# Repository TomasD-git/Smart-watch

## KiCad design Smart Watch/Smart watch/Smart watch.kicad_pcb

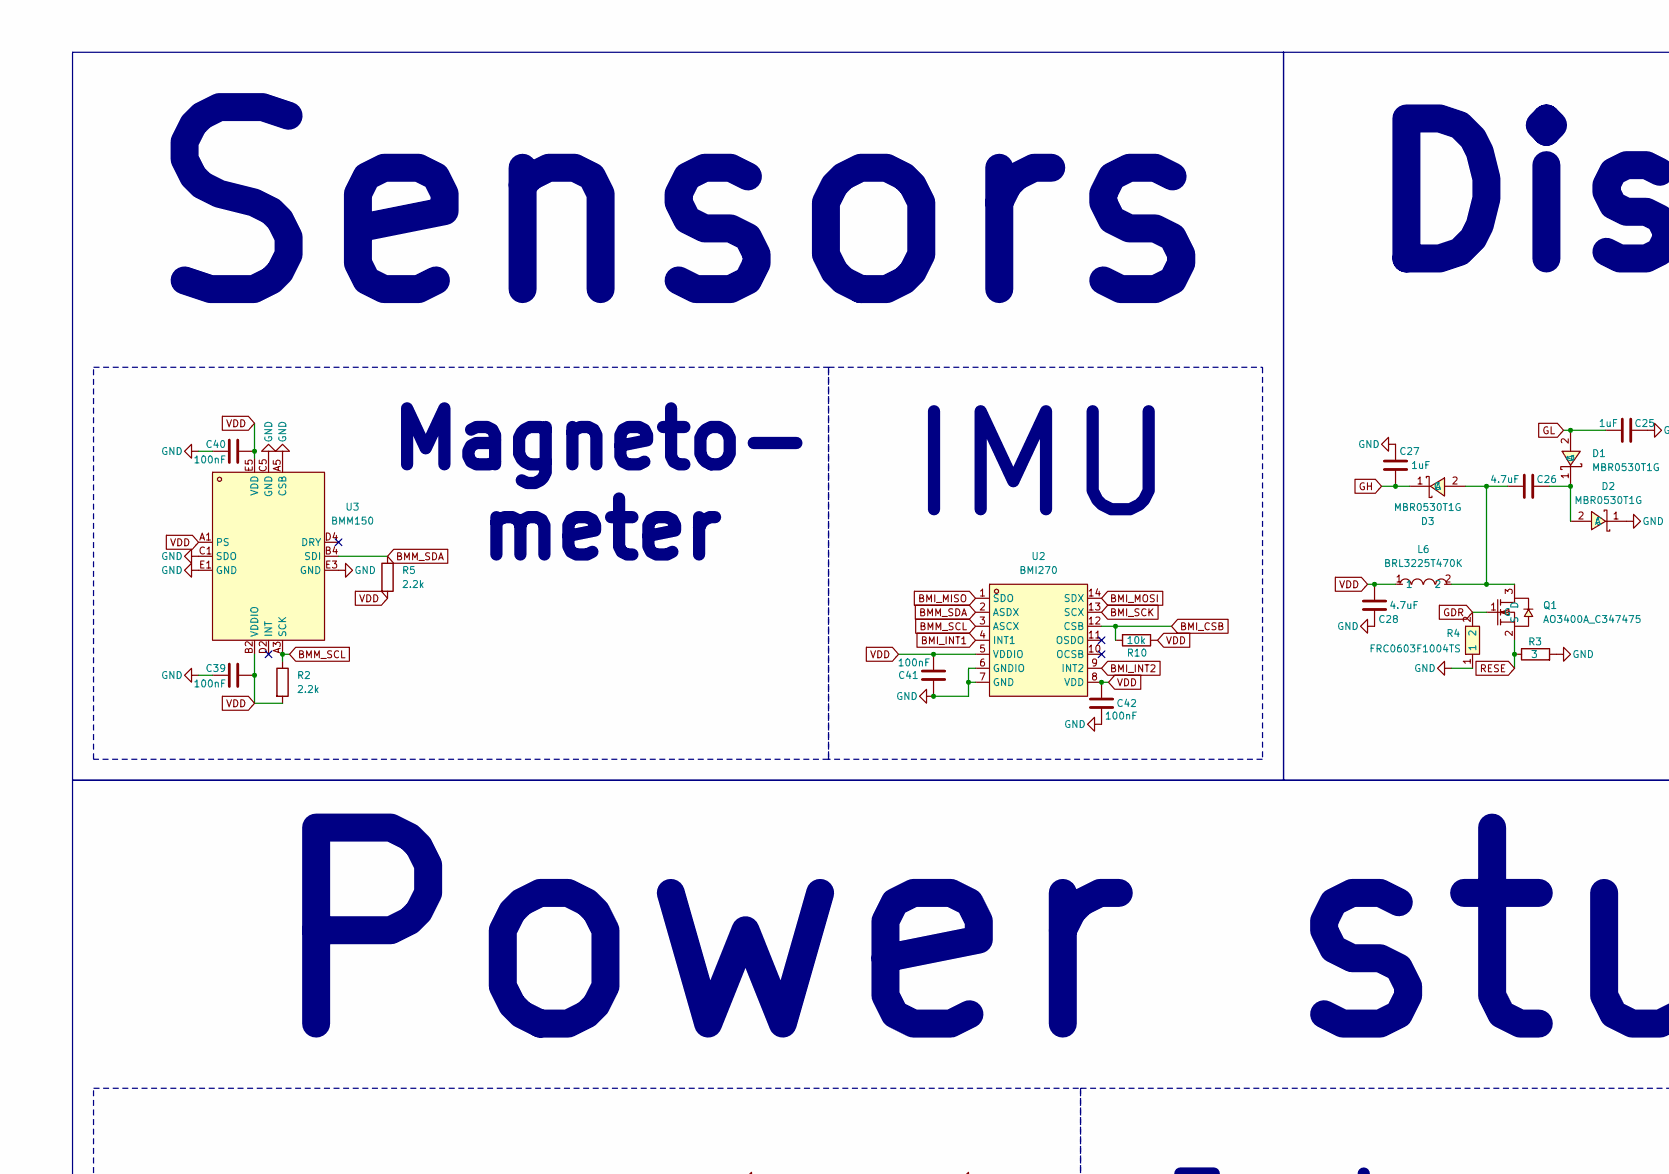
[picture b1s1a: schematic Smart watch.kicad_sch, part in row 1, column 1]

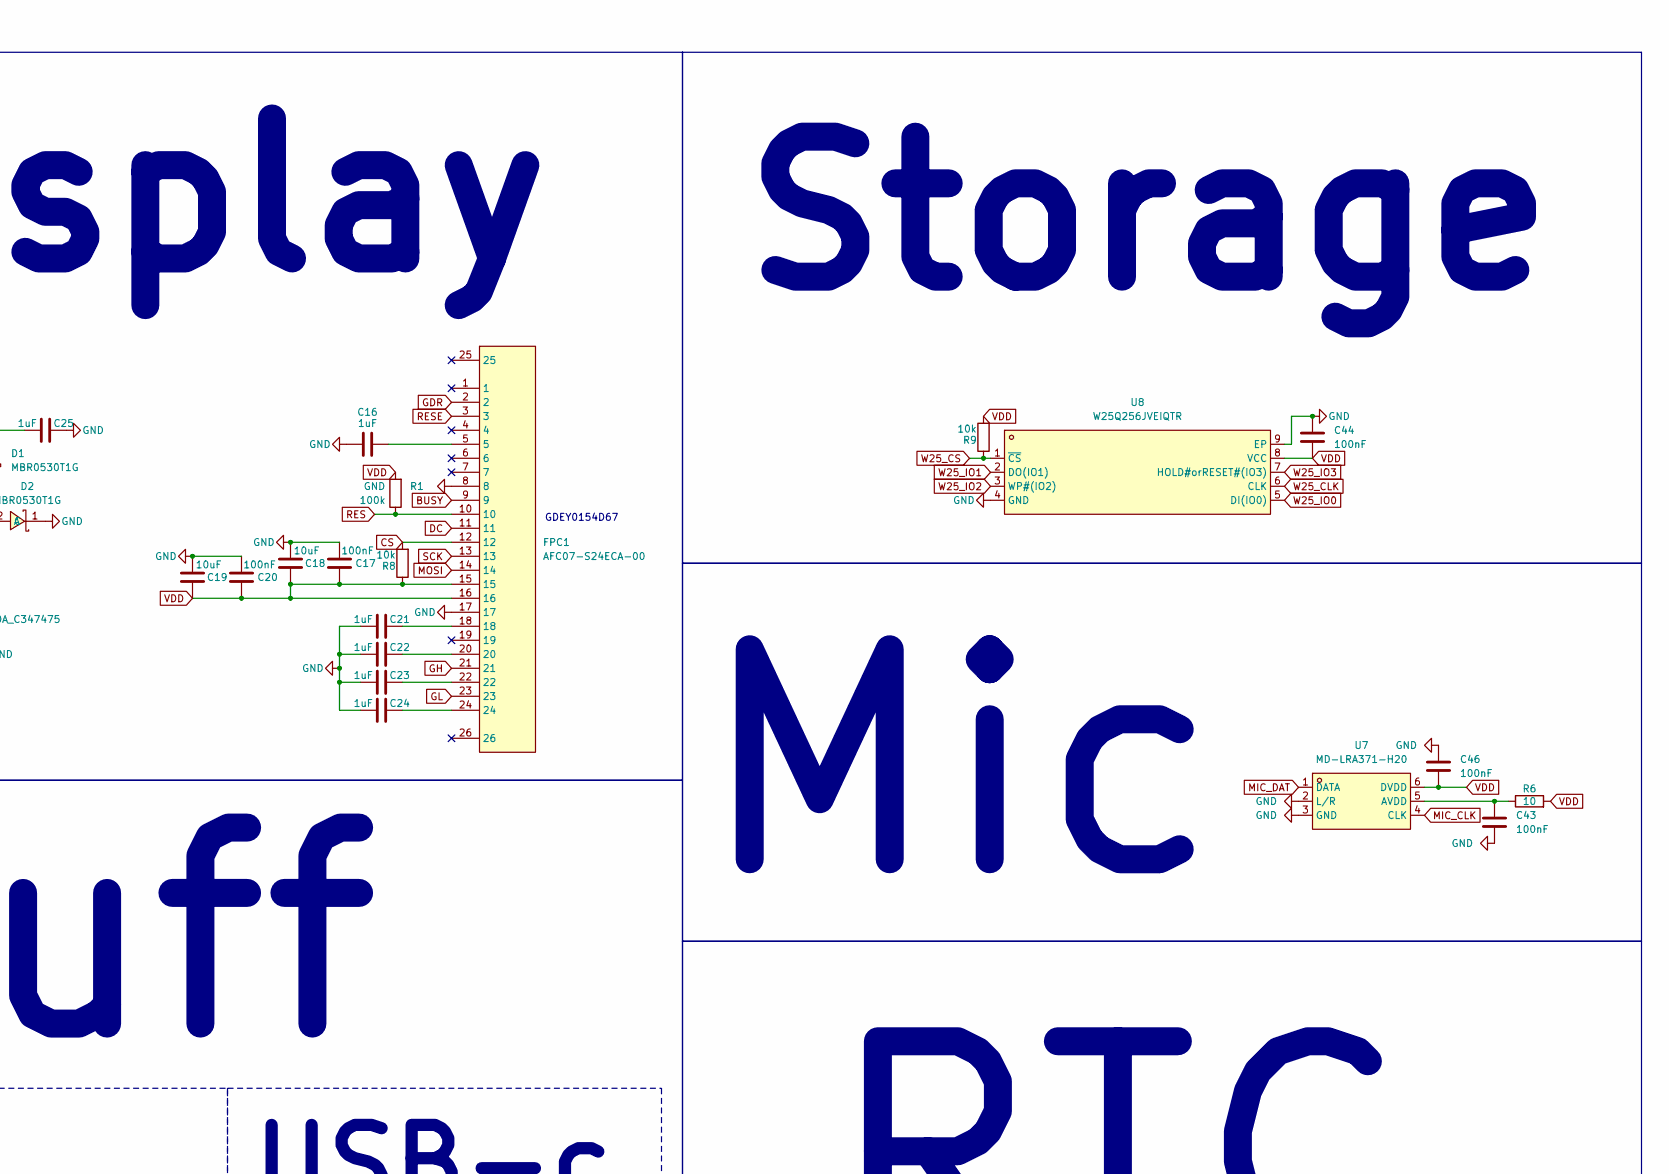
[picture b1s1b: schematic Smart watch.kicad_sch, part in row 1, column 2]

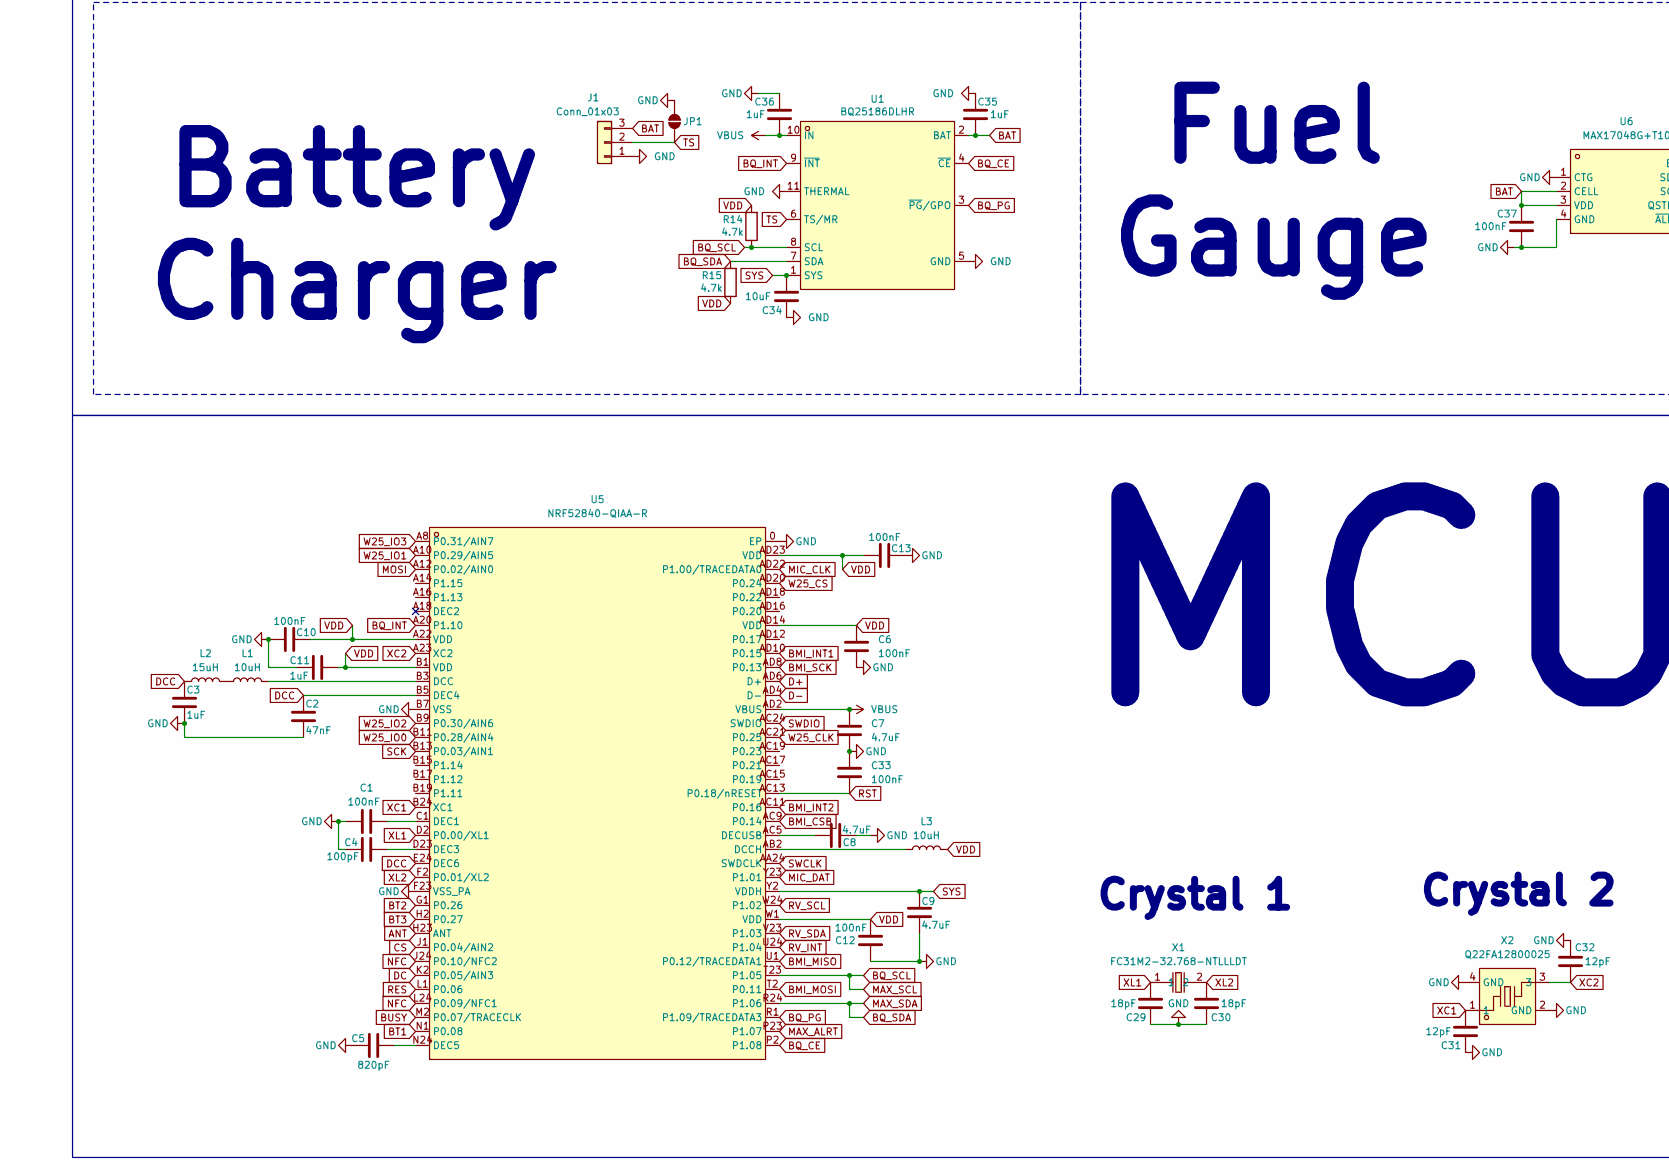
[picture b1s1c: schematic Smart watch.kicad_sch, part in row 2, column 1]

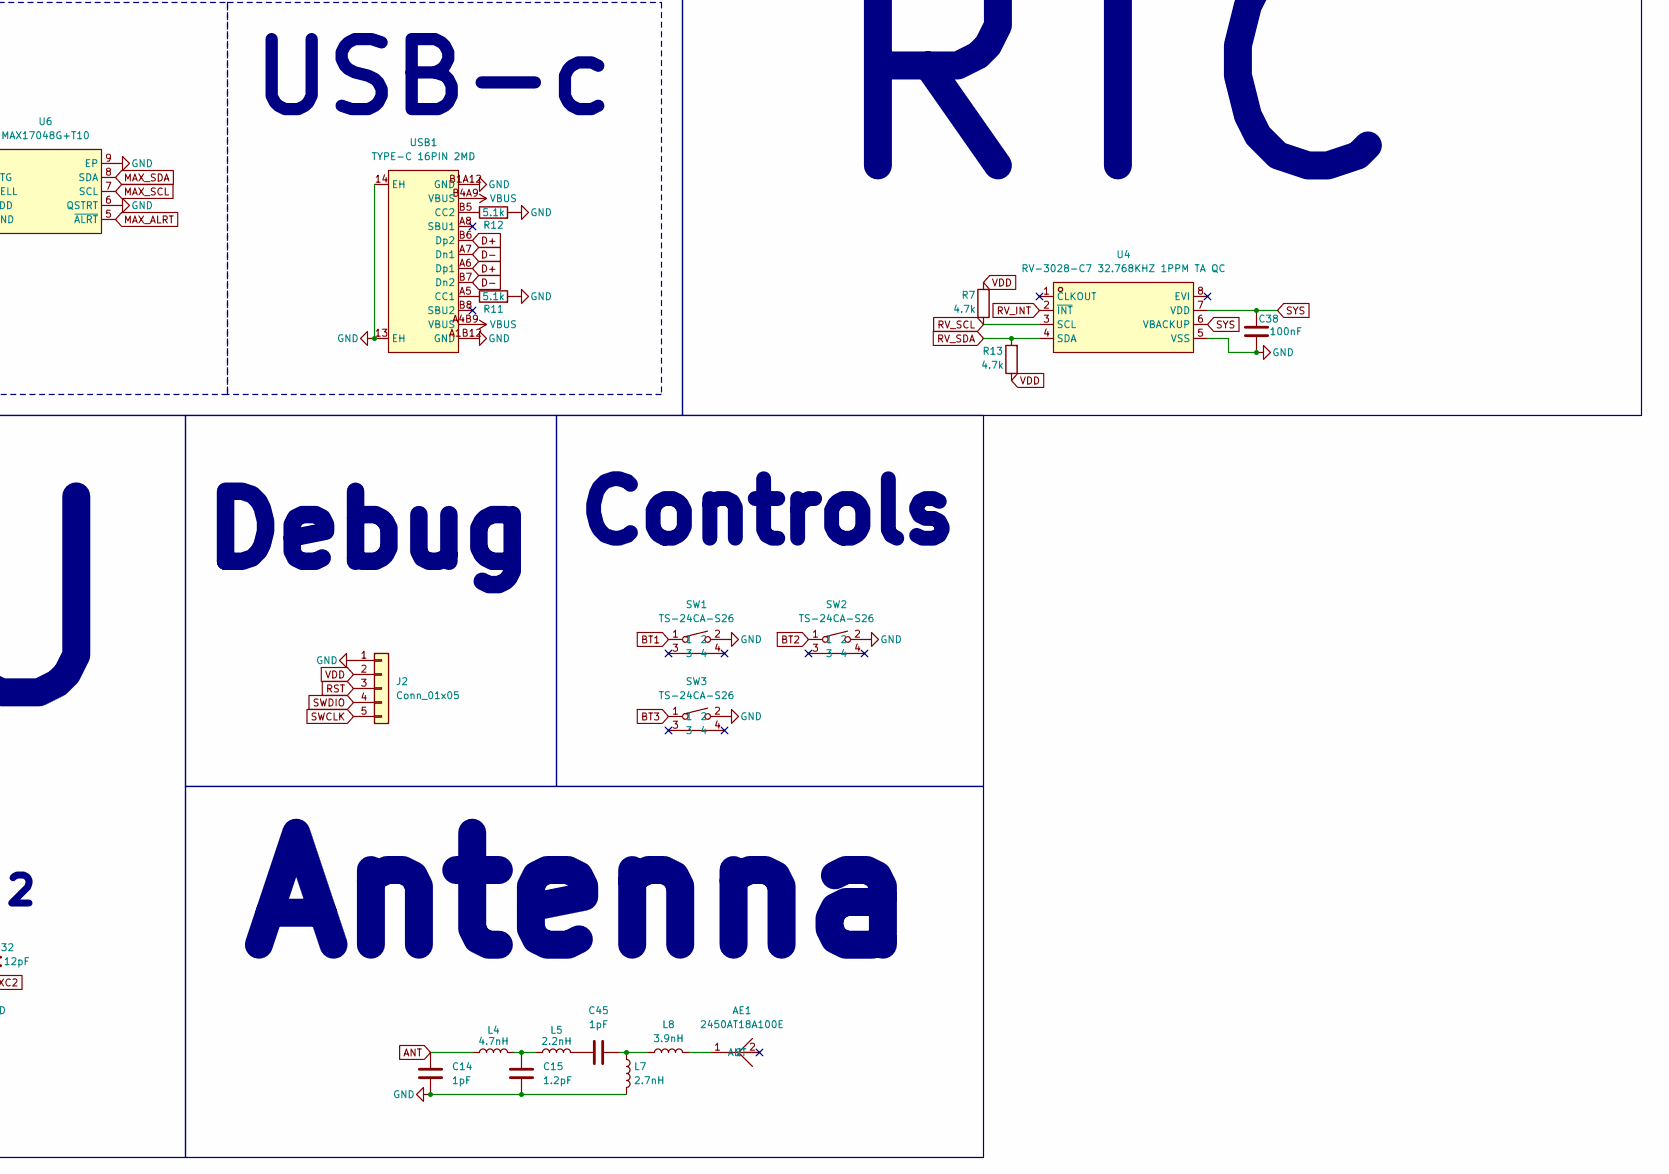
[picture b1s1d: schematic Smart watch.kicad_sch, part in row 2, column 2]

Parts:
AE1: 2450AT18A100E; ANT-SMD_L3.2-W1.6; MPN 2450AT18A100E; LCSC Part C89334
C1, C6, C10, C12, C13, C17, C20, C33, C37, C38, C39, C40, C41, C42, C43, C44, C46: 100nF; C_0402_1005Metric
C2: 47nF; C_0402_1005Metric
C3, C11, C16, C21, C22, C23, C24, C25, C27, C35, C36: 1uF; C_0402_1005Metric
C4: 100pF; C_0402_1005Metric
C5: 820pF; C_0402_1005Metric
C7, C8, C9, C26: 4.7uF; C_0402_1005Metric
C14, C45: 1pF; C_0402_1005Metric
C15: 1.2pF; C_0402_1005Metric
C18, C19, C34: 10uF; C_0603_1608Metric
C28: 4.7uF; C_0603_1608Metric
C29, C30: 18pF; C_0402_1005Metric
C31, C32: 12pF; C_0402_1005Metric
D1, D2, D3: MBR0530T1G; SOD-123_L2.7-W1.6-LS3.7-RD-1; MPN MBR0530T1G; LCSC Part C82046
FPC1: AFC07-S24ECA-00; FPC-SMD_AFC07-S24ECA-00; MPN AFC07-S24ECA-00; LCSC Part C262643
J1: Conn_01x03; PinHeader_1x03_P2.54mm_Vertical
J2: Conn_01x05; PinHeader_1x05_P2.54mm_Vertical
JP1: SolderJumper_2_Open; SolderJumper-2_P1.3mm_Open_RoundedPad1.0x1.5mm
L1, L3: 10uH; L_0805_2012Metric
L2: 15uH; L_0805_2012Metric
L4: 4.7nH; L_0402_1005Metric
L5: 2.2nH; L_0402_1005Metric
L6: BRL3225T470K; IND-SMD_L3.2-W2.5-BRL3225T100M; MPN BRL3225T470K; LCSC Part C524993
L7: 2.7nH; L_0402_1005Metric
L8: 3.9nH; L_0402_1005Metric
Q1: AO3400A_C347475; SOT-23-3_L2.9-W1.3-P1.90-LS2.4-BR; MPN AO3400A; LCSC Part C347475
R1: 100k; R_0603_1608Metric
R2, R5: 2.2k; R_0603_1608Metric
R3: 3; R_0603_1608Metric
R4: FRC0603F1004TS; R0603; MPN FRC0603F1004TS; LCSC Part C2907003
R6: 10; R_0603_1608Metric
R7, R13, R14, R15: 4.7k; R_0603_1608Metric
R8, R9, R10: 10k; R_0603_1608Metric
R11, R12: 5.1k; R_0603_1608Metric
SW1, SW2, SW3: TS-24CA-S26; SW-SMD_L4.7-W3.5-P3.35-EH; MPN TS-24CA-S26; LCSC Part C42420265
U1: BQ25186DLHR; WSON-10_L2.2-W2.0-P0.40-BL-EP_TI_DLH0010A; MPN BQ25186DLHR; LCSC Part C44639442
U2: BMI270; LGA-14_L3.0-W2.5-P0.50-BR; MPN BMI270; LCSC Part C2836813
U3: BMM150; WLCSP-12_L1.6-W1.6_BMM150; MPN BMM150; LCSC Part C171681
U4: RV-3028-C7 32.768KHZ 1PPM TA QC; OSC-SMD_8P-L3.2-W1.5-P0.90-BL; MPN RV-3028-C7-32.768kHz-1ppm-TA-QC; LCSC Part C3019759
U5: NRF52840-QIAA-R; AQFN-73_L7.0-W7.0-P0.50-BL-EP4.8; MPN NRF52840-QIAA-R; LCSC Part C190794
U6: MAX17048G+T10; TDFN-8_L2.0-W2.0-P0.50-BL-EP1.2; MPN MAX17048G+T10; LCSC Part C2682616
U7: MD-LRA371-H20; MIC-SMD_6P-L3.0-W2.3_MD-LRA371-H20; MPN MD-LRA371-H20; LCSC Part C50275770
U8: W25Q256JVEIQTR; WSON-8_L8.0-W6.10-P1.27-BL-EP; MPN W25Q256JVEIQ; LCSC Part C97522
USB1: TYPE-C 16PIN 2MD; USB-C-SMD_TYPE-C-16PIN-2MD-073; MPN TYPE-C 16PIN 2MD(073); LCSC Part C2765186
X1: FC31M2-32.768-NTLLLDT; CRYSTAL-SMD_L3.2-W1.5-1; MPN FC31M2-32.768-NTLLLDT; LCSC Part C2842180
X2: Q22FA12800025; CRYSTAL-SMD_4P-L2.0-W1.6-BL; MPN Q22FA12800025; LCSC Part C187794

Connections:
ANT: C14.1, L4.1, U5.H23 (ANT)
BAT: C35.2, C37.2, J1.3, U1.2 (BAT), U6.2 (CELL), U6.3 (VDD)
BMI_CSB: R10.2, U2.12 (CSB), U5.AC9 (P0.14)
BMI_INT1: U2.4 (INT1), U5.AD10 (P0.15)
BMI_INT2: U2.9 (INT2), U5.AC11 (P0.16)
BMI_MISO: U2.1 (SDO), U5.U1 (P0.12/TRACEDATA1)
BMI_MOSI: U2.14 (SDX), U5.T2 (P0.11)
BMI_SCK: U2.13 (SCX), U5.AD8 (P0.13)
BMM_SCL: R2.1, U2.3 (ASCX), U3.A3 (SCK)
BMM_SDA: R5.1, U2.2 (ASDX), U3.B4 (SDI)
BQ_CE: U1.4 (~CE), U5.P2 (P1.08)
BQ_INT: U1.9 (~INT), U5.A20 (P1.10)
BQ_PG: U1.3 (~PG/GPO), U5.R1 (P1.09/TRACEDATA3)
BQ_SCL: R14.1, U1.8 (SCL), U5.T23 (P1.05), U6.7 (SCL)
BQ_SDA: R15.2, U1.7 (SDA), U5.R24 (P1.06), U6.8 (SDA)
BT1: SW1.1, U5.N1 (P0.08)
BT2: SW2.1, U5.G1 (P0.26)
BT3: SW3.1, U5.H2 (P0.27)
BUSY: FPC1.9, U5.M2 (P0.07/TRACECLK)
CS: FPC1.12, R8.2, U5.J1 (P0.04/AIN2)
D+: U5.AD6 (D+), USB1.A6 (Dp1), USB1.B6 (Dp2)
D-: U5.AD4 (D-), USB1.A7 (Dn1), USB1.B7 (Dn2)
DC: FPC1.11, U5.K2 (P0.05/AIN3)
DCC: C2.1, C3.1, L2.1, U5.B5 (DEC4), U5.E24 (DEC6)
GDR: FPC1.2, Q1.1 (G), R4.2
GH: C27.1, D3.1 (C), FPC1.21
GL: C25.1, D1.2 (A), FPC1.23
GND: C1.1, C2.2, C3.2, C4.1, C5.1, C6.2, C7.2, C8.2, C9.2, C10.1, C11.1, C12.1, C13.2, C14.2, C15.2, C16.1, C17.1, C18.1, C19.1, C20.1, C21.1, C22.1, C23.1, C24.1, C25.2, C27.2, C28.1, C29.2, C30.1, C31.2, C32.2, C33.1, C34.2, C35.1, C36.2, C37.1, C38.1, C39.2, C40.2, C41.1, C42.2, C43.2, C44.1, C46.1, D2.1 (C), FPC1.8, FPC1.17, J1.1, J2.1, JP1.2 (B), L7.2, R3.2, R4.1, R11.2, R12.2, SW1.2, SW2.2, SW3.2, U1.5 (GND), U1.11 (THERMAL), U2.6 (GNDIO), U2.7 (GND), U3.A5 (CSB), U3.C1 (SDO), U3.C5 (GND), U3.E1 (GND), U3.E3 (GND), U4.5 (VSS), U5.0 (EP), U5.B7 (VSS), U5.F23 (VSS_PA), U6.1 (CTG), U6.4 (GND), U6.6 (QSTRT), U6.9 (EP), U7.2 (L/R), U7.3 (GND), U8.4 (GND), U8.9 (EP), USB1.13 (EH), USB1.14 (EH), USB1.A1B12 (GND), USB1.B1A12 (GND), X2.2 (GND), X2.4 (GND)
MAX_ALRT: U5.P23 (P1.07), U6.5 (~ALRT)
MIC_CLK: U5.AD22 (P1.00/TRACEDATA0), U7.4 (CLK)
MIC_DAT: U5.Y23 (P1.01), U7.1 (DATA)
MOSI: FPC1.14, U5.A12 (P0.02/AIN0)
NFC: U5.J24 (P0.10/NFC2), U5.L24 (P0.09/NFC1)
unnamed: AE1.1 (ANT), L8.2
unnamed: C15.1, L4.2, L5.1
unnamed: C16.2, FPC1.5
unnamed: C21.2, FPC1.18
unnamed: C22.2, FPC1.20
unnamed: C23.2, FPC1.22
unnamed: C24.2, FPC1.24
unnamed: C45.1, L5.2
unnamed: C45.2, L7.1, L8.1
unnamed: C26.2, D1.1 (C), D2.2 (A)
unnamed: C26.1, D3.2 (A), L6.2, Q1.3 (D)
unnamed: L1.1, L2.2
unnamed: L1.2, U5.B3 (DCC)
unnamed: L3.1, U5.AB2 (DCCH)
unnamed: C1.2, U5.C1 (DEC1)
unnamed: C4.2, U5.D23 (DEC3)
unnamed: C5.2, U5.N24 (DEC5)
unnamed: C8.1, U5.AC5 (DECUSB)
unnamed: C43.1, R6.1, U7.5 (AVDD)
unnamed: R11.1, USB1.A5 (CC1)
unnamed: R12.1, USB1.B5 (CC2)
RES: FPC1.10, R1.1, U5.L1 (P0.06)
RESE: FPC1.3, Q1.2 (S), R3.1
RST: C33.2, J2.3, U5.AC13 (P0.18/nRESET)
RV_INT: U4.2 (~INT), U5.U24 (P1.04)
RV_SCL: R7.1, U4.3 (SCL), U5.W24 (P1.02)
RV_SDA: R13.2, U4.4 (SDA), U5.V23 (P1.03)
SCK: FPC1.13, U5.B13 (P0.03/AIN1)
SWCLK: J2.5, U5.AA24 (SWDCLK)
SWDIO: J2.4, U5.AC24 (SWDIO)
SYS: C9.1, C34.1, C38.2, U1.1 (SYS), U4.6 (VBACKUP), U4.7 (VDD), U5.Y2 (VDDH)
TS: J1.2, JP1.1 (A), U1.6 (TS/MR)
VBUS: C7.1, C36.1, U1.10 (IN), U5.AD2 (VBUS), USB1.A4B9 (VBUS), USB1.B4A9 (VBUS)
VDD: C6.1, C10.2, C11.2, C12.2, C13.1, C17.2, C18.2, C19.2, C20.2, C28.2, C39.1, C40.1, C41.2, C42.1, C44.2, C46.2, FPC1.15, FPC1.16, J2.2, L3.2, L6.1, R1.2, R2.2, R5.2, R6.2, R7.2, R8.1, R9.2, R10.1, R13.1, R14.2, R15.1, U2.5 (VDDIO), U2.8 (VDD), U3.A1 (PS), U3.B2 (VDDIO), U3.E5 (VDD), U5.A22 (VDD), U5.AD14 (VDD), U5.AD23 (VDD), U5.B1 (VDD), U5.W1 (VDD), U7.6 (DVDD), U8.8 (VCC)
W25_CLK: U5.AC21 (P0.25), U8.6 (CLK)
W25_CS: R9.1, U5.AD20 (P0.24), U8.1 (~CS)
W25_IO0: U5.B11 (P0.28/AIN4), U8.5 (DI(IO0))
W25_IO1: U5.A10 (P0.29/AIN5), U8.2 (DO(IO1))
W25_IO2: U5.B9 (P0.30/AIN6), U8.3 (WP#(IO2))
W25_IO3: U5.A8 (P0.31/AIN7), U8.7 (HOLD#orRESET#(IO3))
XC1: C31.1, U5.B24 (XC1), X2.1
XC2: C32.1, U5.A23 (XC2), X2.3
XL1: C29.1, U5.D2 (P0.00/XL1), X1.1
XL2: C30.2, U5.F2 (P0.01/XL2), X1.2

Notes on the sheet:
Crystal 2
Controls
Storage
RTC
Mic
Power stuff
Display
Magneto- meter
IMU
Sensors
MCU
GDEY0154D67
Fuel Gauge
Battery Charger
Crystal 1
Antenna
USB-c
Debug

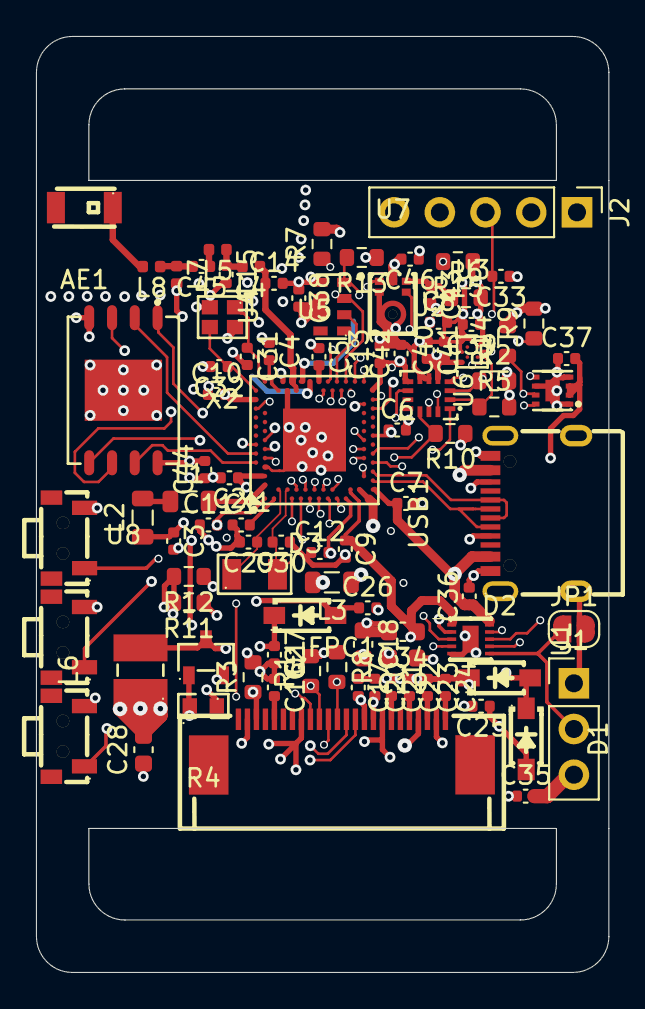
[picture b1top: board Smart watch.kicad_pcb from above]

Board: 6 copper layers, 31.8 x 52.0 mm, 92 parts (0 on the bottom side), 77 nets.
